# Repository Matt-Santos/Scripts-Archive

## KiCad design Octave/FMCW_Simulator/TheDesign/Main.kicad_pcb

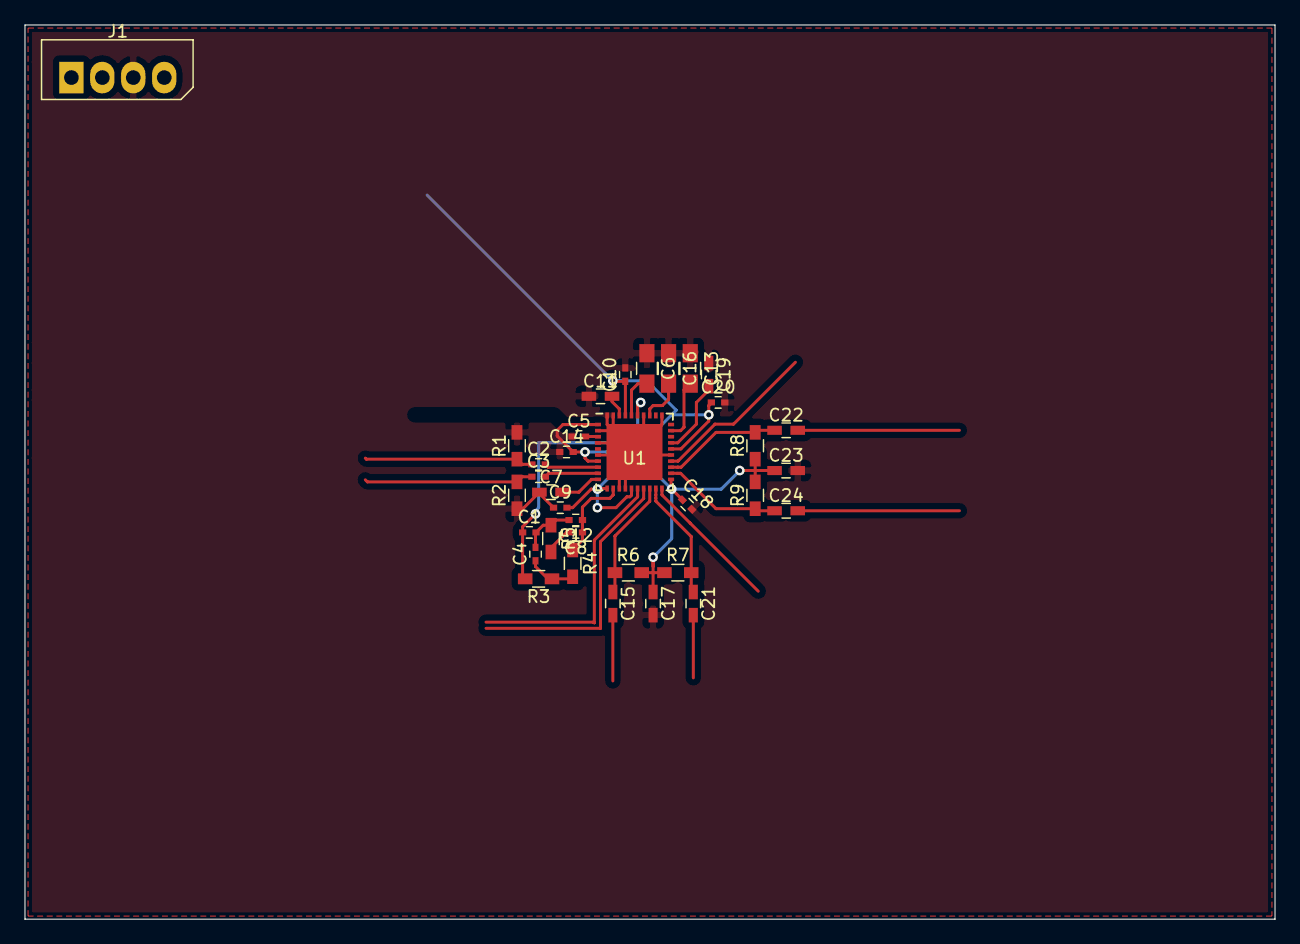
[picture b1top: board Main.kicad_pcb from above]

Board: 2 copper layers, 102.6 x 73.4 mm, 35 parts (0 on the bottom side), 22 nets.

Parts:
C1, C2, C3, C4, C5, C8, C9, C10, C12, C14, C18, C20: 0.1u; C0402C104K8PACTU
C6, C13, C16: 10u; C0805C106K9PACTU
C7, C11, C19: 1u; C0603C105K8PACTU
C15, C17, C21, C22, C23, C24: 100p; C0603C101K5RACTU
J1: Conn_01x04; Molex_SPOX-5267_22-03-5045_04x2.54mm_Straight
R1, R2, R3, R4, R5, R6, R7, R8, R9: 50; FC0603E50R0BST1
U1: LMX2582

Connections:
0: C5.1, C6.1, C7.1, C9.1, C10.2, C11.1, C13.1, C14.1, C16.1, C17.2, C18.2, C19.1, C20.2, C23.2, J1.3, R1.2, R2.1, U1.2, U1.4, U1.6, U1.13, U1.14, U1.25, U1.31, U1.34, U1.39, U1.40, U1.41
/HF_VCO/OSCinM: C3.1, R2.2
/HF_VCO/OSCinP: C2.1, R1.1
/HF_VCO/Vcc: C9.2, C10.1, C14.2, C17.1, C18.1, C20.1, C23.1, J1.4, R6.2, R7.1, R8.1, R9.2, U1.1, U1.7, U1.11, U1.15, U1.21, U1.26, U1.37
/HF_VCO/Vtune: C1.1, R3.2, U1.35
unnamed: C1.2, C4.2, C12.2, R5.1
unnamed: C2.2, U1.8
unnamed: C3.2, U1.9
unnamed: C4.1, R3.1, R4.2
unnamed: C5.2, U1.3
unnamed: C6.2, U1.36
unnamed: C7.2, U1.10
unnamed: C8.2, R5.2
unnamed: C11.2, U1.38
unnamed: C8.1, C12.1, R4.1, U1.12
unnamed: C13.2, U1.29
unnamed: C15.1, R6.1, U1.18
unnamed: C16.2, U1.33
unnamed: C19.2, U1.27
unnamed: C21.1, R7.2, U1.19
unnamed: C22.1, R8.2, U1.23
unnamed: C24.1, R9.1, U1.22

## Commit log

2017-12-24 Add in all current scripts, sorted by application
2024-12-31 feat: add content
2025-01-10 feat: add project readme
2025-04-07 add: additional FMCW files
